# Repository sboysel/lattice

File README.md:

# lattice

## hardware

WCH CH552T
Wurth 452403012014
Korean Hroparts Elec K3-1390S-E1
https://www.lcsc.com/product-detail/Slide-Switches_Korean-Hroparts-Elec-K3-1390S-D1_C223854.html

https://www.lcsc.com/product-detail/span-style-background-color-ff0-Analog-span-Switches-Multiplexers_Texas-Instruments-TS3A44159PWR_C151886.html
https://www.lcsc.com/products/Analog-Switches-Multiplexers_618.html?Number%20of%20Channels=%5B%224%22%5D&Switch%20Circuit=%5B%22SPDT%28SPDT%29%22%5D

C&K PCM12SMTR C221841

# TODO

- toggle sidedness
- https://github.com/qmk/qmk_firmware/blob/master/docs/serial_driver.md#pin-configuration-2

## license

Copyright 2024 Sam Boysel

Hardware: CERN-OHL-P. Software: BSD-3-Clause.

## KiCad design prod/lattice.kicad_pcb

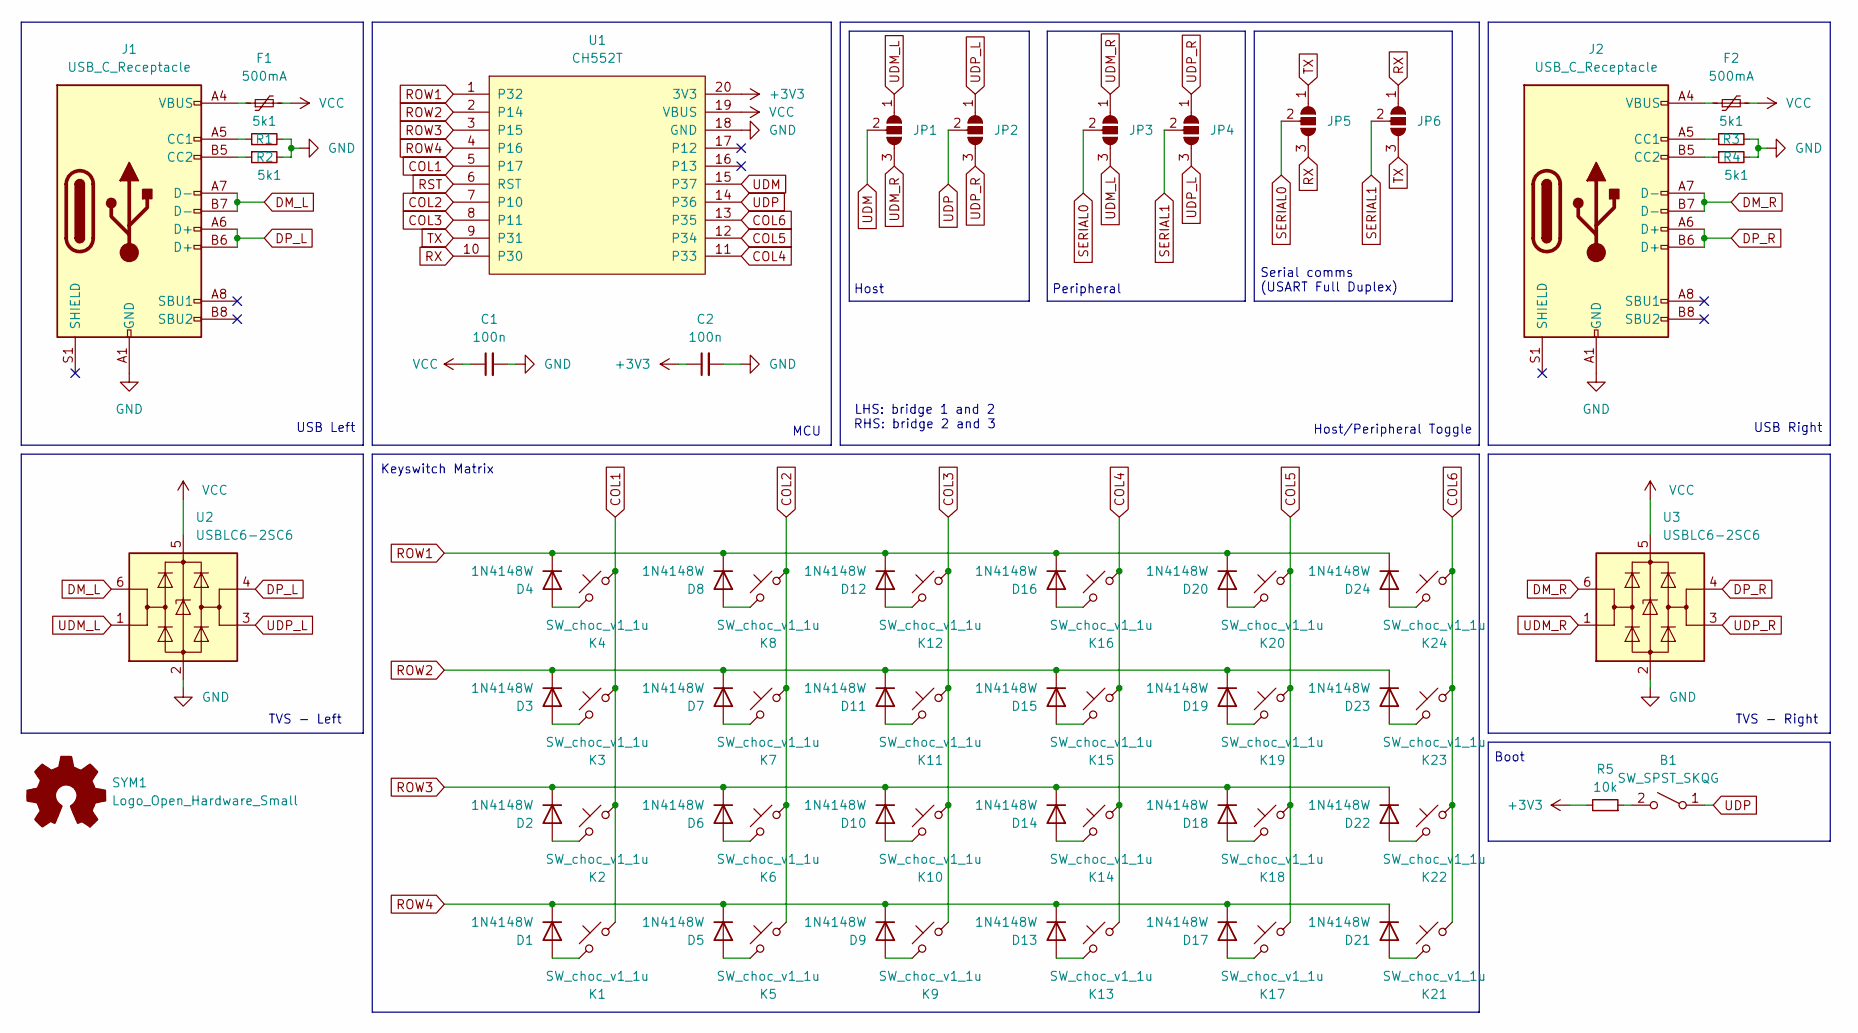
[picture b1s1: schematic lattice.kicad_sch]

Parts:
B1: SW_SPST_SKQG; SW_SPST_SKQG_WithStem
C1, C2: 100n; C_0805_2012Metric_Pad1.18x1.45mm_HandSolder
D1, D2, D3, D4, D5, D6, D7, D8, D9, D10, D11, D12, D13, D14, D15, D16, D17, D18, D19, D20, D21, D22, D23, D24: 1N4148W; D_SOD-123_via
F1, F2: 500mA; Fuse_0805_2012Metric_Pad1.15x1.40mm_HandSolder
J1, J2: USB_C_Receptacle; USB_C_Receptacle_HRO_TYPE-C-31-M-12
JP1, JP2, JP3, JP4, JP5, JP6: SolderJumper_3_Open; SolderJumper-3_P1.3mm_Open_RoundedPad1.0x1.5mm
K1, K2, K3, K4, K5, K6, K7, K8, K9, K10, K11, K12, K13, K14, K15, K16, K17, K18, K19, K20, K21, K22, K23, K24: SW_choc_v1_1u
R1, R2, R3, R4: 5k1; R_0805_2012Metric_Pad1.20x1.40mm_HandSolder
R5: 10k; R_0805_2012Metric_Pad1.20x1.40mm_HandSolder
SYM1: Logo_Open_Hardware_Small; OSHW-Logo_5.7x6mm_SilkScreen
U1: CH552T; TSSOP-20_4.4x6.5mm_P0.65mm
U2, U3: USBLC6-2SC6; SOT-23-6_Handsoldering

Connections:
+3V3: C2.1, R5.2, U1.20 (3V3)
COL1: K1.1, K2.1, K3.1, K4.1, U1.5 (P17)
COL2: K5.1, K6.1, K7.1, K8.1, U1.7 (P10)
COL3: K9.1, K10.1, K11.1, K12.1, U1.8 (P11)
COL4: K13.1, K14.1, K15.1, K16.1, U1.11 (P33)
COL5: K17.1, K18.1, K19.1, K20.1, U1.12 (P34)
COL6: K21.1, K22.1, K23.1, K24.1, U1.13 (P35)
DM_L: J1.A7 (D-), J1.B7 (D-), U2.6 (I/O1)
DM_R: J2.A7 (D-), J2.B7 (D-), U3.6 (I/O1)
DP_L: J1.A6 (D+), J1.B6 (D+), U2.4 (I/O2)
DP_R: J2.A6 (D+), J2.B6 (D+), U3.4 (I/O2)
GND: C1.2, C2.2, J1.A1 (GND), J1.A12 (GND), J1.B1 (GND), J1.B12 (GND), J2.A1 (GND), J2.A12 (GND), J2.B1 (GND), J2.B12 (GND), R1.2, R2.2, R3.2, R4.2, U1.18 (GND), U2.2 (GND), U3.2 (GND)
unnamed: B1.2 (B), R5.1
unnamed: D1.2 (A), K1.2
unnamed: D2.2 (A), K2.2
unnamed: D3.2 (A), K3.2
unnamed: D4.2 (A), K4.2
unnamed: D5.2 (A), K5.2
unnamed: D6.2 (A), K6.2
unnamed: D7.2 (A), K7.2
unnamed: D8.2 (A), K8.2
unnamed: D9.2 (A), K9.2
unnamed: D10.2 (A), K10.2
unnamed: D11.2 (A), K11.2
unnamed: D12.2 (A), K12.2
unnamed: D13.2 (A), K13.2
unnamed: D14.2 (A), K14.2
unnamed: D15.2 (A), K15.2
unnamed: D16.2 (A), K16.2
unnamed: D17.2 (A), K17.2
unnamed: D18.2 (A), K18.2
unnamed: D19.2 (A), K19.2
unnamed: D20.2 (A), K20.2
unnamed: D21.2 (A), K21.2
unnamed: D22.2 (A), K22.2
unnamed: D23.2 (A), K23.2
unnamed: D24.2 (A), K24.2
unnamed: F1.1, J1.A4 (VBUS), J1.A9 (VBUS), J1.B4 (VBUS), J1.B9 (VBUS)
unnamed: F2.1, J2.A4 (VBUS), J2.A9 (VBUS), J2.B4 (VBUS), J2.B9 (VBUS)
unnamed: J1.A5 (CC1), R1.1
unnamed: J1.B5 (CC2), R2.1
unnamed: J2.A5 (CC1), R3.1
unnamed: J2.B5 (CC2), R4.1
ROW1: D4.1 (K), D8.1 (K), D12.1 (K), D16.1 (K), D20.1 (K), D24.1 (K), U1.1 (P32)
ROW2: D3.1 (K), D7.1 (K), D11.1 (K), D15.1 (K), D19.1 (K), D23.1 (K), U1.2 (P14)
ROW3: D2.1 (K), D6.1 (K), D10.1 (K), D14.1 (K), D18.1 (K), D22.1 (K), U1.3 (P15)
ROW4: D1.1 (K), D5.1 (K), D9.1 (K), D13.1 (K), D17.1 (K), D21.1 (K), U1.4 (P16)
RST: U1.6 (RST)
RX: JP5.3 (B), JP6.1 (A), U1.10 (P30)
SERIAL0: JP3.2 (C), JP5.2 (C)
SERIAL1: JP4.2 (C), JP6.2 (C)
TX: JP5.1 (A), JP6.3 (B), U1.9 (P31)
UDM: JP1.2 (C), U1.15 (P37)
UDM_L: JP1.1 (A), JP3.3 (B), U2.1 (I/O1)
UDM_R: JP1.3 (B), JP3.1 (A), U3.1 (I/O1)
UDP: B1.1 (A), JP2.2 (C), U1.14 (P36)
UDP_L: JP2.1 (A), JP4.3 (B), U2.3 (I/O2)
UDP_R: JP2.3 (B), JP4.1 (A), U3.3 (I/O2)
VCC: C1.1, F1.2, F2.2, U1.19 (VBUS), U2.5 (VBUS), U3.5 (VBUS)

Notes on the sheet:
Host/Peripheral Toggle
Peripheral
Keyswitch Matrix
Serial comms (USART Full Duplex)
USB Right
TVS - Right
LHS: bridge 1 and 2 RHS: bridge 2 and 3
MCU
Boot
Host
USB Left
TVS - Left

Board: 2 copper layers, 70 parts (1 on the bottom side), 58 nets, no tracks yet.

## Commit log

2024-02-18 inital commit
2024-02-18 matrix finished
2024-02-18 silkscreen text
2024-02-19 placing major rp2040 components
2024-02-19 more work on schematic
2024-02-19 schematic done, most components placed
2024-02-20 components placed
2024-02-20 adding breakout header
2024-02-20 placement adjustments
2024-02-20 preoject-specific 3dmodels and footprints
2024-02-20 component placement
2024-02-20 component placement (swap crystal and flash)
2024-02-21 component placement (swap rp2040 and flash)
2024-03-06 trying ch552t version
2024-03-06 more complete schematic
2024-03-07 schematic work
2024-03-07 schematic pretty solid
2024-03-08 4 channel mux/demux
2024-03-08 license update
2025-01-25 CFX spacing, solder jumpers
2025-01-25 boot button, remove refereence designators, jumper labels
2025-01-25 jumper label as footprint
